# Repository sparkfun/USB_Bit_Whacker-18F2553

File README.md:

USB Bit Whacker - 18F2553 Development Board
========================================

[*USB Bit Whacker - 18F2553 Development Board (DEV-00762)*](https://www.sparkfun.com/products/762)

The USB Bit Whacker is a spectacular little development board featuring the PIC18F2553.
 Based on the work of Brian Schmalz, the UBW is a small board with a command interpreter for basic input and output control. 
 When attached to a Windows/Max OS X/Linux computer, the UBW will show up as an RS232 Com port! 
You control the individual I/O pins on the PIC through simple serial commands.

Repository Contents
-------------------

* **/Hardware** - Eagle design files (.brd, .sch)
* **/Production** - Production panel files (.brd)

Documentation
--------------
* **[Product Home Page](http://www.schmalzhaus.com/UBW/index.html)** - Schmalz Haus site for the UBW.
* **[SparkFun Fritzing repo](https://github.com/sparkfun/Fritzing_Parts)** - Fritzing diagrams for SparkFun products.
* **[SparkFun 3D Model repo](https://github.com/sparkfun/3D_Models)** - 3D models of SparkFun products. 

License Information
-------------------
This product is _**open source**_! 

Please use, reuse, and modify these files as you see fit. Please maintain attribution to SparkFun Electronics and release anything derivative under the same license.

Distributed as-is; no warranty is given.

- Your friends at SparkFun.

_**Note:** This product is a collaboration with Brian Schmalz. A portion of each sales goes back to them for product support and continued development._

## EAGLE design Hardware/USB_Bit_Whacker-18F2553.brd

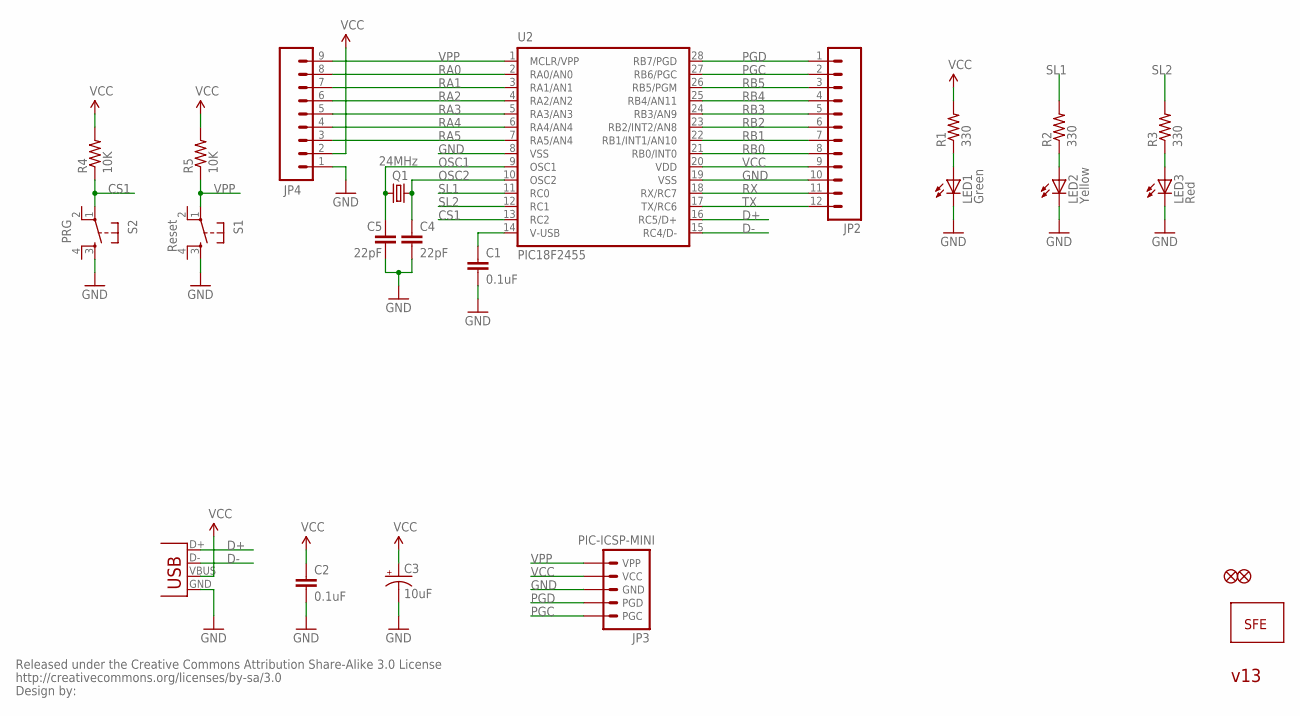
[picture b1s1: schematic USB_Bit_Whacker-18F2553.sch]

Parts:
C1, C2: 0.1uF; 0402-CAP
C3: 10uF; EIA3216
C4, C5: 22pF; 0402-CAP
FID1, FID2: FIDUCIAL1X2; FIDUCIAL-1X2
JP2: M12PTH; 1X12
JP3: PIC-ICSP-MINI
JP4: M09; 1X09
LED1: Green; LED-1206
LED2: Yellow; LED-1206
LED3: Red; LED-1206
Q1: 24MHz; CRYSTAL-SMD-5X3
R1, R2, R3: 330; 0402-RES
R4, R5: 10K; 0402-RES
S1: Reset; TACTILE_SWITCH_SMD
S2: PRG; TACTILE_SWITCH_SMD
U2: PIC18F2455; SO-28W
U$1: LOGO-SFENEW; SFE-NEW-WEBLOGO
U$2: CREATIVE_COMMONS
X1: USBSMD; USB-MINIB

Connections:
CS1: R4.1, S2.1, U2.13 (RC2)
D+: U2.16 (RC5/D+), X1.D+
D-: U2.15 (RC4/D-), X1.D-
GND: C1.2, C2.2, C3.C (-), C4.2, C5.2, JP2.10, JP3.3 (GND), JP4.1, LED1.C, LED2.C, LED3.C, S1.3, S2.3, U2.8 (VSS), U2.19 (VSS), X1.GND
unnamed: C1.1, U2.14 (V-USB)
unnamed: LED1.A, R1.1
unnamed: LED2.A, R2.1
unnamed: LED3.A, R3.1
OSC1: C5.1, Q1.3 (2), U2.9 (OSC1)
OSC2: C4.1, Q1.1, U2.10 (OSC2)
PGC: JP2.2, JP3.5 (PGC), U2.27 (RB6/PGC)
PGD: JP2.1, JP3.4 (PGD), U2.28 (RB7/PGD)
RA0: JP4.8, U2.2 (RA0/AN0)
RA1: JP4.7, U2.3 (RA1/AN1)
RA2: JP4.6, U2.4 (RA2/AN2)
RA3: JP4.5, U2.5 (RA3/AN3)
RA4: JP4.4, U2.6 (RA4/AN4)
RA5: JP4.3, U2.7 (RA5/AN4)
RB0: JP2.8, U2.21 (RB0/INT0)
RB1: JP2.7, U2.22 (RB1/INT1/AN10)
RB2: JP2.6, U2.23 (RB2/INT2/AN8)
RB3: JP2.5, U2.24 (RB3/AN9)
RB4: JP2.4, U2.25 (RB4/AN11)
RB5: JP2.3, U2.26 (RB5/PGM)
RX: JP2.11, U2.18 (RX/RC7)
SL1: R2.2, U2.11 (RC0)
SL2: R3.2, U2.12 (RC1)
TX: JP2.12, U2.17 (TX/RC6)
VCC: C2.1, C3.A (+), JP2.9, JP3.2 (VCC), JP4.2, R1.2, R4.2, R5.2, U2.20 (VDD), X1.VBUS
VPP: JP3.1 (VPP), JP4.9, R5.1, S1.1, U2.1 (MCLR/VPP)

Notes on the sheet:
v13

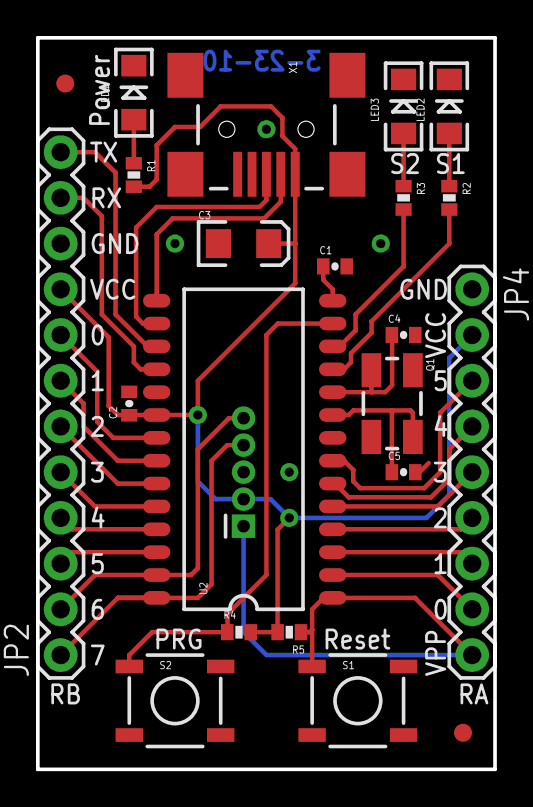
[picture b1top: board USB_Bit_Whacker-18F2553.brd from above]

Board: 2 copper layers, 25.4 x 40.6 mm, 25 parts (1 on the bottom side), 30 nets.

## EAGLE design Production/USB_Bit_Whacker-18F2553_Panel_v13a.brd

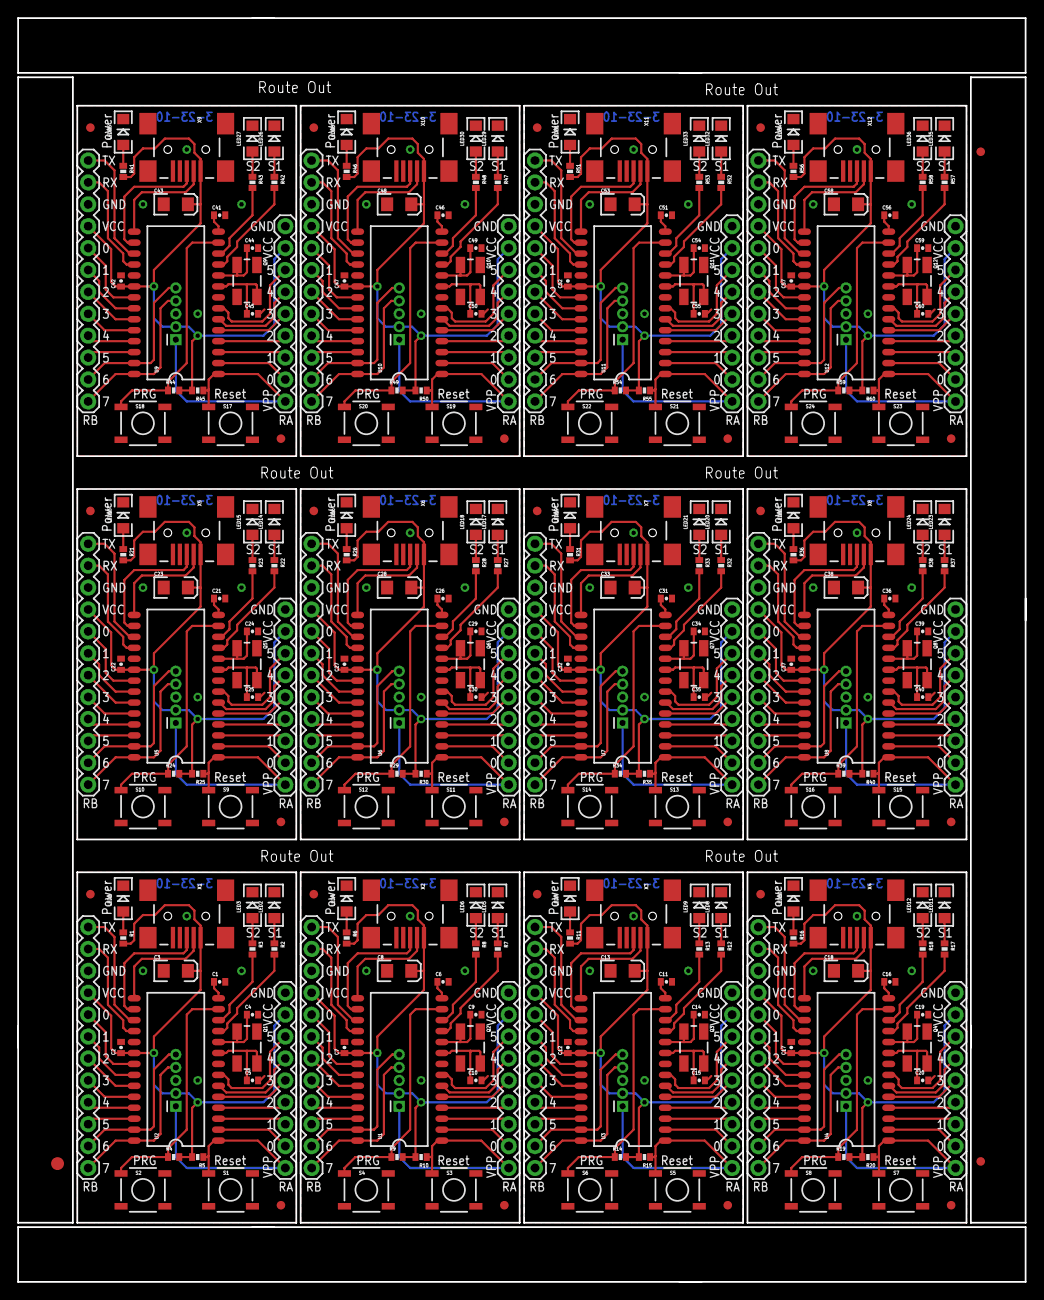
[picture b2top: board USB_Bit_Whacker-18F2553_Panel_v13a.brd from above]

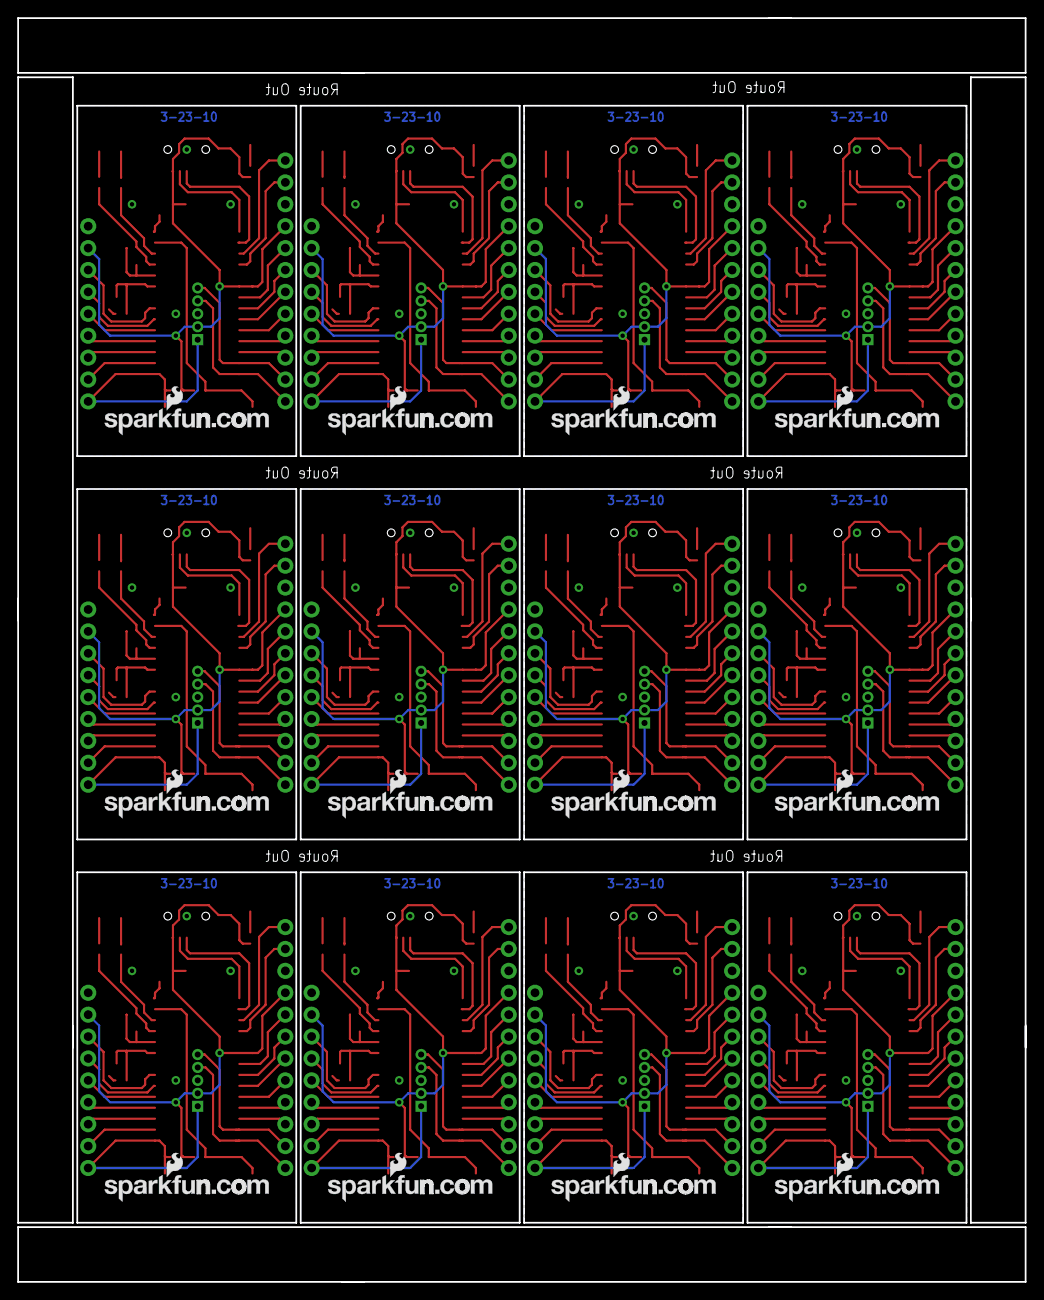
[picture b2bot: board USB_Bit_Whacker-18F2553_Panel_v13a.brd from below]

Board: 2 copper layers, 116.8 x 146.6 mm, 291 parts (12 on the bottom side), 360 nets.

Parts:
C1, C2, C6, C7, C11, C12, C16, C17, C21, C22, C26, C27, C31, C32, C36, C37, C41, C42, C46, C47, C51, C52, C56, C57: 0.1uF; 0402-CAP
C3, C8, C13, C18, C23, C28, C33, C38, C43, C48, C53, C58: 10uF; EIA3216
C4, C5, C9, C10, C14, C15, C19, C20, C24, C25, C29, C30, C34, C35, C39, C40, C44, C45, C49, C50, C54, C55, C59, C60: 22pF; 0402-CAP
E$1: FIDUCIAL-1.5X3
E$7, E$8: FIDUCIAL-1X2
FID1, FID2, FID3, FID4, FID5, FID6, FID7, FID8, FID9, FID10, FID11, FID12, FID13, FID14, FID15, FID16, FID17, FID18, FID19, FID20, FID21, FID22, FID23, FID24: FIDUCIAL1X2; FIDUCIAL-1X2
JP1, JP2, JP7, JP10, JP13, JP16, JP19, JP22, JP25, JP28, JP31, JP34: 1X12
JP3, JP5, JP8, JP11, JP14, JP17, JP20, JP23, JP26, JP29, JP32, JP35: PIC-ICSP-MINI
JP4, JP6, JP9, JP12, JP15, JP18, JP21, JP24, JP27, JP30, JP33, JP36: 1X09
LED1, LED4, LED7, LED10, LED13, LED16, LED19, LED22, LED25, LED28, LED31, LED34: Green; LED-1206
LED2, LED5, LED8, LED11, LED14, LED17, LED20, LED23, LED26, LED29, LED32, LED35: Yellow; LED-1206
LED3, LED6, LED9, LED12, LED15, LED18, LED21, LED24, LED27, LED30, LED33, LED36: Red; LED-1206
Q1, Q2, Q3, Q4, Q5, Q6, Q7, Q8, Q9, Q10, Q11, Q12: 24MHz; CRYSTAL-SMD-5X3
R1, R2, R3, R6, R7, R8, R11, R12, R13, R16, R17, R18, R21, R22, R23, R26, R27, R28, R31, R32, R33, R36, R37, R38, R41, R42, R43, R46, R47, R48, R51, R52, R53, R56, R57, R58: 330; 0402-RES
R4, R5, R9, R10, R14, R15, R19, R20, R24, R25, R29, R30, R34, R35, R39, R40, R44, R45, R49, R50, R54, R55, R59, R60: 10K; 0402-RES
S1, S3, S5, S7, S9, S11, S13, S15, S17, S19, S21, S23: Reset; TACTILE_SWITCH_SMD
S2, S4, S6, S8, S10, S12, S14, S16, S18, S20, S22, S24: PRG; TACTILE_SWITCH_SMD
U1, U2, U3, U4, U5, U6, U7, U8, U9, U10, U11, U12: PIC18F2455; SO-28W
U$1, U$2, U$3, U$4, U$5, U$6, U$7, U$8, U$9, U$10, U$11, U$12: LOGO-SFENEW; SFE-NEW-WEBLOGO
X1, X2, X3, X4, X5, X6, X7, X8, X9, X10, X11, X12: USBSMD; USB-MINIB

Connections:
CS1: R4.1, S2.1, U2.13
CS2: R9.1, S4.1, U1.13
CS3: R14.1, S6.1, U3.13
CS4: R19.1, S8.1, U4.13
CS5: R24.1, S10.1, U5.13
CS6: R29.1, S12.1, U6.13
CS7: R34.1, S14.1, U7.13
CS8: R39.1, S16.1, U8.13
CS9: R44.1, S18.1, U9.13
CS10: R49.1, S20.1, U10.13
CS11: R54.1, S22.1, U11.13
CS12: R59.1, S24.1, U12.13
D+: U2.16, X1.D+
D+1: U1.16, X2.D+
D+2: U3.16, X3.D+
D+3: U4.16, X4.D+
D+4: U5.16, X5.D+
D+5: U6.16, X6.D+
D+6: U7.16, X7.D+
D+7: U8.16, X8.D+
D+8: U9.16, X9.D+
D+9: U10.16, X10.D+
D+10: U11.16, X11.D+
D+11: U12.16, X12.D+
D-: U2.15, X1.D-
D-1: U1.15, X2.D-
D-2: U3.15, X3.D-
D-3: U4.15, X4.D-
D-4: U5.15, X5.D-
D-5: U6.15, X6.D-
D-6: U7.15, X7.D-
D-7: U8.15, X8.D-
D-8: U9.15, X9.D-
D-9: U10.15, X10.D-
D-10: U11.15, X11.D-
D-11: U12.15, X12.D-
GND: C1.2, C2.2, C3.C, C4.2, C5.2, JP2.10, JP3.3, JP4.1, LED1.C, LED2.C, LED3.C, S1.3, S2.3, U2.8, U2.19, X1.GND
GND1: C6.2, C7.2, C8.C, C9.2, C10.2, JP1.10, JP5.3, JP6.1, LED4.C, LED5.C, LED6.C, S3.3, S4.3, U1.8, U1.19, X2.GND
GND2: C11.2, C12.2, C13.C, C14.2, C15.2, JP7.10, JP8.3, JP9.1, LED7.C, LED8.C, LED9.C, S5.3, S6.3, U3.8, U3.19, X3.GND
GND3: C16.2, C17.2, C18.C, C19.2, C20.2, JP10.10, JP11.3, JP12.1, LED10.C, LED11.C, LED12.C, S7.3, S8.3, U4.8, U4.19, X4.GND
GND4: C21.2, C22.2, C23.C, C24.2, C25.2, JP13.10, JP14.3, JP15.1, LED13.C, LED14.C, LED15.C, S9.3, S10.3, U5.8, U5.19, X5.GND
GND5: C26.2, C27.2, C28.C, C29.2, C30.2, JP16.10, JP17.3, JP18.1, LED16.C, LED17.C, LED18.C, S11.3, S12.3, U6.8, U6.19, X6.GND
GND6: C31.2, C32.2, C33.C, C34.2, C35.2, JP19.10, JP20.3, JP21.1, LED19.C, LED20.C, LED21.C, S13.3, S14.3, U7.8, U7.19, X7.GND
GND7: C36.2, C37.2, C38.C, C39.2, C40.2, JP22.10, JP23.3, JP24.1, LED22.C, LED23.C, LED24.C, S15.3, S16.3, U8.8, U8.19, X8.GND
GND8: C41.2, C42.2, C43.C, C44.2, C45.2, JP25.10, JP26.3, JP27.1, LED25.C, LED26.C, LED27.C, S17.3, S18.3, U9.8, U9.19, X9.GND
GND9: C46.2, C47.2, C48.C, C49.2, C50.2, JP28.10, JP29.3, JP30.1, LED28.C, LED29.C, LED30.C, S19.3, S20.3, U10.8, U10.19, X10.GND
GND10: C51.2, C52.2, C53.C, C54.2, C55.2, JP31.10, JP32.3, JP33.1, LED31.C, LED32.C, LED33.C, S21.3, S22.3, U11.8, U11.19, X11.GND
GND11: C56.2, C57.2, C58.C, C59.2, C60.2, JP34.10, JP35.3, JP36.1, LED34.C, LED35.C, LED36.C, S23.3, S24.3, U12.8, U12.19, X12.GND
unnamed: C1.1, U2.14
unnamed: C6.1, U1.14
unnamed: LED4.A, R6.1
unnamed: LED1.A, R1.1
unnamed: LED2.A, R2.1
unnamed: LED3.A, R3.1
unnamed: LED5.A, R7.1
unnamed: LED6.A, R8.1
unnamed: C11.1, U3.14
unnamed: LED7.A, R11.1
unnamed: LED8.A, R12.1
unnamed: LED9.A, R13.1
unnamed: C16.1, U4.14
unnamed: LED10.A, R16.1
unnamed: LED11.A, R17.1
unnamed: LED12.A, R18.1
unnamed: C21.1, U5.14
unnamed: LED13.A, R21.1
unnamed: LED14.A, R22.1
unnamed: LED15.A, R23.1
unnamed: C26.1, U6.14
unnamed: LED16.A, R26.1
unnamed: LED17.A, R27.1
unnamed: LED18.A, R28.1
unnamed: C31.1, U7.14
unnamed: LED19.A, R31.1
unnamed: LED20.A, R32.1
unnamed: LED21.A, R33.1
unnamed: C36.1, U8.14
unnamed: LED22.A, R36.1
unnamed: LED23.A, R37.1
unnamed: LED24.A, R38.1
unnamed: C41.1, U9.14
unnamed: LED25.A, R41.1
unnamed: LED26.A, R42.1
unnamed: LED27.A, R43.1
unnamed: C46.1, U10.14
unnamed: LED28.A, R46.1
unnamed: LED29.A, R47.1
unnamed: LED30.A, R48.1
unnamed: C51.1, U11.14
unnamed: LED31.A, R51.1
unnamed: LED32.A, R52.1
unnamed: LED33.A, R53.1
unnamed: C56.1, U12.14
unnamed: LED34.A, R56.1
unnamed: LED35.A, R57.1
unnamed: LED36.A, R58.1
OSC1: C5.1, Q1.3, U2.9
OSC2: C4.1, Q1.1, U2.10
OSC3: C9.1, Q2.1, U1.10
OSC4: C10.1, Q2.3, U1.9
OSC5: C14.1, Q3.1, U3.10
OSC6: C15.1, Q3.3, U3.9
OSC7: C19.1, Q4.1, U4.10
OSC8: C20.1, Q4.3, U4.9
OSC9: C24.1, Q5.1, U5.10
OSC10: C25.1, Q5.3, U5.9
OSC11: C29.1, Q6.1, U6.10
OSC12: C30.1, Q6.3, U6.9
OSC13: C34.1, Q7.1, U7.10
OSC14: C35.1, Q7.3, U7.9
OSC15: C39.1, Q8.1, U8.10
OSC16: C40.1, Q8.3, U8.9
OSC17: C44.1, Q9.1, U9.10
OSC18: C45.1, Q9.3, U9.9
OSC19: C49.1, Q10.1, U10.10
OSC20: C50.1, Q10.3, U10.9
OSC21: C54.1, Q11.1, U11.10
OSC22: C55.1, Q11.3, U11.9
OSC23: C59.1, Q12.1, U12.10
OSC24: C60.1, Q12.3, U12.9
PGC: JP2.2, JP3.5, U2.27
PGC1: JP1.2, JP5.5, U1.27
PGC2: JP7.2, JP8.5, U3.27
PGC3: JP10.2, JP11.5, U4.27
PGC4: JP13.2, JP14.5, U5.27
PGC5: JP16.2, JP17.5, U6.27
PGC6: JP19.2, JP20.5, U7.27
PGC7: JP22.2, JP23.5, U8.27
PGC8: JP25.2, JP26.5, U9.27
PGC9: JP28.2, JP29.5, U10.27
PGC10: JP31.2, JP32.5, U11.27
PGC11: JP34.2, JP35.5, U12.27
PGD: JP2.1, JP3.4, U2.28
PGD1: JP1.1, JP5.4, U1.28
PGD2: JP7.1, JP8.4, U3.28
PGD3: JP10.1, JP11.4, U4.28
PGD4: JP13.1, JP14.4, U5.28
PGD5: JP16.1, JP17.4, U6.28
PGD6: JP19.1, JP20.4, U7.28
PGD7: JP22.1, JP23.4, U8.28
PGD8: JP25.1, JP26.4, U9.28
PGD9: JP28.1, JP29.4, U10.28
PGD10: JP31.1, JP32.4, U11.28
PGD11: JP34.1, JP35.4, U12.28
RA0: JP4.8, U2.2
RA1: JP4.7, U2.3
RA2: JP4.6, U2.4
RA3: JP4.5, U2.5
RA4: JP4.4, U2.6
RA5: JP4.3, U2.7
RA6: JP6.8, U1.2
RA7: JP6.7, U1.3
RA8: JP6.6, U1.4
RA9: JP6.5, U1.5
RA10: JP6.4, U1.6
RA11: JP6.3, U1.7
RA12: JP9.8, U3.2
RA13: JP9.7, U3.3
RA14: JP9.6, U3.4
RA15: JP9.5, U3.5
RA16: JP9.4, U3.6
RA17: JP9.3, U3.7
RA18: JP12.8, U4.2
RA19: JP12.7, U4.3
RA20: JP12.6, U4.4
RA21: JP12.5, U4.5
RA22: JP12.4, U4.6
RA23: JP12.3, U4.7
RA24: JP15.8, U5.2
RA25: JP15.7, U5.3
RA26: JP15.6, U5.4
RA27: JP15.5, U5.5
RA28: JP15.4, U5.6
RA29: JP15.3, U5.7
RA30: JP18.8, U6.2
RA31: JP18.7, U6.3
RA32: JP18.6, U6.4
RA33: JP18.5, U6.5
RA34: JP18.4, U6.6
RA35: JP18.3, U6.7
RA36: JP21.8, U7.2
RA37: JP21.7, U7.3
RA38: JP21.6, U7.4
RA39: JP21.5, U7.5
RA40: JP21.4, U7.6
RA41: JP21.3, U7.7
RA42: JP24.8, U8.2
RA43: JP24.7, U8.3
RA44: JP24.6, U8.4
RA45: JP24.5, U8.5
RA46: JP24.4, U8.6
RA47: JP24.3, U8.7
RA48: JP27.8, U9.2
RA49: JP27.7, U9.3
RA50: JP27.6, U9.4
RA51: JP27.5, U9.5
RA52: JP27.4, U9.6
RA53: JP27.3, U9.7
RA54: JP30.8, U10.2
RA55: JP30.7, U10.3
RA56: JP30.6, U10.4
RA57: JP30.5, U10.5
RA58: JP30.4, U10.6
RA59: JP30.3, U10.7
RA60: JP33.8, U11.2
RA61: JP33.7, U11.3
RA62: JP33.6, U11.4
RA63: JP33.5, U11.5
RA64: JP33.4, U11.6
RA65: JP33.3, U11.7
RA66: JP36.8, U12.2
RA67: JP36.7, U12.3
RA68: JP36.6, U12.4
RA69: JP36.5, U12.5
RA70: JP36.4, U12.6
RA71: JP36.3, U12.7
RB0: JP2.8, U2.21
RB1: JP2.7, U2.22
RB2: JP2.6, U2.23
RB3: JP2.5, U2.24
RB4: JP2.4, U2.25
RB5: JP2.3, U2.26
RB6: JP1.3, U1.26
RB7: JP1.4, U1.25
RB8: JP1.5, U1.24
RB9: JP1.6, U1.23
RB10: JP1.7, U1.22
RB11: JP1.8, U1.21
RB12: JP7.3, U3.26
RB13: JP7.4, U3.25
RB14: JP7.5, U3.24
RB15: JP7.6, U3.23
RB16: JP7.7, U3.22
RB17: JP7.8, U3.21
RB18: JP10.3, U4.26
RB19: JP10.4, U4.25
RB20: JP10.5, U4.24
RB21: JP10.6, U4.23
RB22: JP10.7, U4.22
RB23: JP10.8, U4.21
RB24: JP13.3, U5.26
RB25: JP13.4, U5.25
RB26: JP13.5, U5.24
RB27: JP13.6, U5.23
RB28: JP13.7, U5.22
RB29: JP13.8, U5.21
RB30: JP16.3, U6.26
RB31: JP16.4, U6.25
RB32: JP16.5, U6.24
RB33: JP16.6, U6.23
RB34: JP16.7, U6.22
RB35: JP16.8, U6.21
RB36: JP19.3, U7.26
RB37: JP19.4, U7.25
RB38: JP19.5, U7.24
RB39: JP19.6, U7.23
RB40: JP19.7, U7.22
RB41: JP19.8, U7.21
RB42: JP22.3, U8.26
RB43: JP22.4, U8.25
RB44: JP22.5, U8.24
RB45: JP22.6, U8.23
RB46: JP22.7, U8.22
RB47: JP22.8, U8.21
RB48: JP25.3, U9.26
RB49: JP25.4, U9.25
RB50: JP25.5, U9.24
RB51: JP25.6, U9.23
RB52: JP25.7, U9.22
RB53: JP25.8, U9.21
RB54: JP28.3, U10.26
RB55: JP28.4, U10.25
RB56: JP28.5, U10.24
RB57: JP28.6, U10.23
RB58: JP28.7, U10.22
RB59: JP28.8, U10.21
RB60: JP31.3, U11.26
RB61: JP31.4, U11.25
RB62: JP31.5, U11.24
RB63: JP31.6, U11.23
RB64: JP31.7, U11.22
RB65: JP31.8, U11.21
RB66: JP34.3, U12.26
RB67: JP34.4, U12.25
RB68: JP34.5, U12.24
RB69: JP34.6, U12.23
RB70: JP34.7, U12.22
RB71: JP34.8, U12.21
RX: JP2.11, U2.18
RX1: JP1.11, U1.18
RX2: JP7.11, U3.18
RX3: JP10.11, U4.18
RX4: JP13.11, U5.18
RX5: JP16.11, U6.18
RX6: JP19.11, U7.18
RX7: JP22.11, U8.18
RX8: JP25.11, U9.18
RX9: JP28.11, U10.18
RX10: JP31.11, U11.18
RX11: JP34.11, U12.18
SL1: R2.2, U2.11
SL2: R3.2, U2.12
SL3: R7.2, U1.11
SL4: R8.2, U1.12
SL5: R12.2, U3.11
SL6: R13.2, U3.12
SL7: R17.2, U4.11
SL8: R18.2, U4.12
SL9: R22.2, U5.11
SL10: R23.2, U5.12
SL11: R27.2, U6.11
SL12: R28.2, U6.12
SL13: R32.2, U7.11
SL14: R33.2, U7.12
SL15: R37.2, U8.11
SL16: R38.2, U8.12
SL17: R42.2, U9.11
SL18: R43.2, U9.12
SL19: R47.2, U10.11
SL20: R48.2, U10.12
SL21: R52.2, U11.11
SL22: R53.2, U11.12
SL23: R57.2, U12.11
SL24: R58.2, U12.12
TX: JP2.12, U2.17
TX1: JP1.12, U1.17
TX2: JP7.12, U3.17
TX3: JP10.12, U4.17
TX4: JP13.12, U5.17
TX5: JP16.12, U6.17
TX6: JP19.12, U7.17
TX7: JP22.12, U8.17
TX8: JP25.12, U9.17
TX9: JP28.12, U10.17
TX10: JP31.12, U11.17
TX11: JP34.12, U12.17
VCC: C2.1, C3.A, JP2.9, JP3.2, JP4.2, R1.2, R4.2, R5.2, U2.20, X1.VBUS
VCC1: C7.1, C8.A, JP1.9, JP5.2, JP6.2, R6.2, R9.2, R10.2, U1.20, X2.VBUS
VCC2: C12.1, C13.A, JP7.9, JP8.2, JP9.2, R11.2, R14.2, R15.2, U3.20, X3.VBUS
VCC3: C17.1, C18.A, JP10.9, JP11.2, JP12.2, R16.2, R19.2, R20.2, U4.20, X4.VBUS
VCC4: C22.1, C23.A, JP13.9, JP14.2, JP15.2, R21.2, R24.2, R25.2, U5.20, X5.VBUS
VCC5: C27.1, C28.A, JP16.9, JP17.2, JP18.2, R26.2, R29.2, R30.2, U6.20, X6.VBUS
VCC6: C32.1, C33.A, JP19.9, JP20.2, JP21.2, R31.2, R34.2, R35.2, U7.20, X7.VBUS
VCC7: C37.1, C38.A, JP22.9, JP23.2, JP24.2, R36.2, R39.2, R40.2, U8.20, X8.VBUS
VCC8: C42.1, C43.A, JP25.9, JP26.2, JP27.2, R41.2, R44.2, R45.2, U9.20, X9.VBUS
VCC9: C47.1, C48.A, JP28.9, JP29.2, JP30.2, R46.2, R49.2, R50.2, U10.20, X10.VBUS
VCC10: C52.1, C53.A, JP31.9, JP32.2, JP33.2, R51.2, R54.2, R55.2, U11.20, X11.VBUS
VCC11: C57.1, C58.A, JP34.9, JP35.2, JP36.2, R56.2, R59.2, R60.2, U12.20, X12.VBUS
VPP: JP3.1, JP4.9, R5.1, S1.1, U2.1
VPP1: JP5.1, JP6.9, R10.1, S3.1, U1.1
VPP2: JP8.1, JP9.9, R15.1, S5.1, U3.1
VPP3: JP11.1, JP12.9, R20.1, S7.1, U4.1
VPP4: JP14.1, JP15.9, R25.1, S9.1, U5.1
VPP5: JP17.1, JP18.9, R30.1, S11.1, U6.1
VPP6: JP20.1, JP21.9, R35.1, S13.1, U7.1
VPP7: JP23.1, JP24.9, R40.1, S15.1, U8.1
VPP8: JP26.1, JP27.9, R45.1, S17.1, U9.1
VPP9: JP29.1, JP30.9, R50.1, S19.1, U10.1
VPP10: JP32.1, JP33.9, R55.1, S21.1, U11.1
VPP11: JP35.1, JP36.9, R60.1, S23.1, U12.1

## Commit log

2015-05-11 Adding hardware files
2015-12-10 added board fiducials
2015-12-10 created panel v13a

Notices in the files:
parts and their libraries:
SparkFun: Released under the Creative Commons Attribution Share-Alike 3.0 License
SparkFun: http://creativecommons.org/licenses/by-sa/3.0
SparkFun-Aesthetics: Licensing: Creative Commons ShareAlike 4.0 International - https://creativecommons.org/licenses/by-sa/4.0
